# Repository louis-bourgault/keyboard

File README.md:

# keyboard
*my project for hack club blueprint*

## Render (made in blender, not exact but this is what I'm going for. I had some fun with lighting in this one)

### Boring edition without the lighting

My design for a lily58 inspired split wireless keyboard using ergogen and kicad. It uses the NRF52840 chipset, and 3d printed parts mostly

One of my friends has significant wrist pain because his laptop keyboard is terrible. A few months ago we were planning to make a keyboard together and made things in Ergogen but never got that much further than that. Now, I have put things into kicad and done a bit more work in preparing things to be actually manufactured.
This is designed to be pretty much as cheap a keyboard as it is possible to manufacture, aiming for about AU$50 per keyboard (I am making two of these, so more like $100 total). This comes out to about $30 USD per keyboard, $60 total.

## Design
### PCB
- Ergogen for PCB design and layout drafting. It is a very simple, user friendly and powerful program. You define layouts for rows and columns, and nets to connect them
  - Note: In my Ergogen file there is a single net that was not correct, and I had to route manually in KiCad. This is the upper thumb cluster key.
- KiCad for routing the pcb. Ergogen creates the nets, so I only have to route it -- as such, there is no kicad schematic file, just a pcb file that I edited to design
- PCB: AllPcb. They had a cheap offer which let me get everything for a $2, including delivery.

### Case Design:
I use Fusion 360 in school, and am quite used to the program, so that is what I will use. As of November 1 2025, I haven't fully decided on the design -- but what I am thinking is that i will use a clean looking white coloured case, with an oiled plywood or even Jarrah laser cut bottom plate that fits in. My school has a good 3d printer (bambu p1s) and a laser cutter, so I can get everything designed there.
Ergogen outputs a DXF file for the bottom shape of the case, which is defined through the ```outlines``` section of ergogen.yml. This is the shape that I use for the outline of my PCB, so I will need to make an offset line around and use that as the case outline.
Also, since I will be taking this keyboard to and from school, I will make a hinging case to place the two halves in with foam padding for safety.

### Software
I will probably just go with zmk for this. One thing that is important to me is for the keyboard to run both wired and wireless - eg I plug one half with a usb C to A port into a school computer, and then that half talks to the other half and I can use it on computers without Bluetooth support; but I believe that QMK has this function so I will just use that. Potentially, if I have extra time, then I could code something custom in C, but I am not sure whether this is feasible at this point and with exams coming up.

Note: this software is in a seperate repo because of the way that ZMK works. The repo is [louis-bourgault/zmk-config](https://github.com/louis-bourgault/zmk-config)

# Images

# Bill of Materials

|Component Type       |Item Link                                                 |Quantity needed|Relevant Specifications       |Tax % (if not included)|Price each (AUD)|Total Cost (AUD)|Total Cost (USD) (using 1 AUD = 0.65 USD)|Running Cost (AUD|Running Cost (USD)|Note                                                                                                                                                       |
|---------------------|----------------------------------------------------------|---------------|------------------------------|-----------------------|----------------|----------------|-----------------------------------------|-----------------|------------------|-----------------------------------------------------------------------------------------------------------------------------------------------------------|
|Battery * 4          |https://www.aliexpress.com/item/1005006924508264.html?mp=1|1              |3.7v, 400mAh, 53x36x6mm, JSTPH|0.00%                  |$18.40          |$18.40          |$11.96                                   |$18.40           |$11.96            |                                                                                                                                                           |
|NRF52840             |https://www.aliexpress.com/item/1005006035267231.html?    |4              |                              |10.00%                 |$5.65           |$24.86          |$16.16                                   |$43.26           |$28.12            |                                                                                                                                                           |
|Keyboard Switch * 110|https://www.aliexpress.com/item/1005006376024657.html?mp=1|1              |Gateron Brown * 110           |10.00%                 |$18.33          |$20.16          |$13.11                                   |$63.42           |$41.22            |This is using my Welcome Deal on Aliexpress                                                                                                                |
|Keyboard Switch * 10 |https://www.aliexpress.com/item/1005006376024657.html?mp=1|1              |Gateron Yellow * 10           |10.00%                 |$4.70           |$5.17           |$3.36                                    |$68.59           |$44.59            |Supplemental Switches, not on welcome deal so substantially more expensive. Will use different type of switch (linear instead of tactile) for modifier keys|
|Diodes * 200         |https://www.aliexpress.com/item/1005009896621714.html     |1              |Basic 1n4148 diodes           |10.00%                 |$5.94           |$6.53           |$4.25                                    |$75.13           |$48.83            |                                                                                                                                                           |
|PCB * 5              |AllPCB                                                    |1              |                              |0.00%                  |$2.14           |$2.14           |$1.39                                    |$77.27           |$50.22            |already purchased                                                                                                                                          |
|Keycaps * 80         |https://www.aliexpress.com/item/1005007415198959.html?mp=1|2              |                              |10.00%                 |$13.58          |$29.88          |$19.42                                   |$107.14          |$69.64            |                                                                                                                                                           |

# Note on Pricing
Since a lot of these sites have little fees that are hard to deal with on a one by one basis (such as payment processing fees, et cetera). So, the final numbers as given at checkout are slightly different.
Additionally, there is a chance that these prices may fluctuate. If they go up at all, I am able to cover the cost (I am willing to spend a bit of my money on this, and don't need a grant for all of it).

Note: this order actually cost me $2.14, it's just not showing the right amount because that was a one time discount

Prices:
- Aliexpress: AU$114.54
- Allpcb: AU$2.14

Total: AU$116.68
In USD: US$76.20
Note: if I do not qualify for a full support, i can cover a portion of it.

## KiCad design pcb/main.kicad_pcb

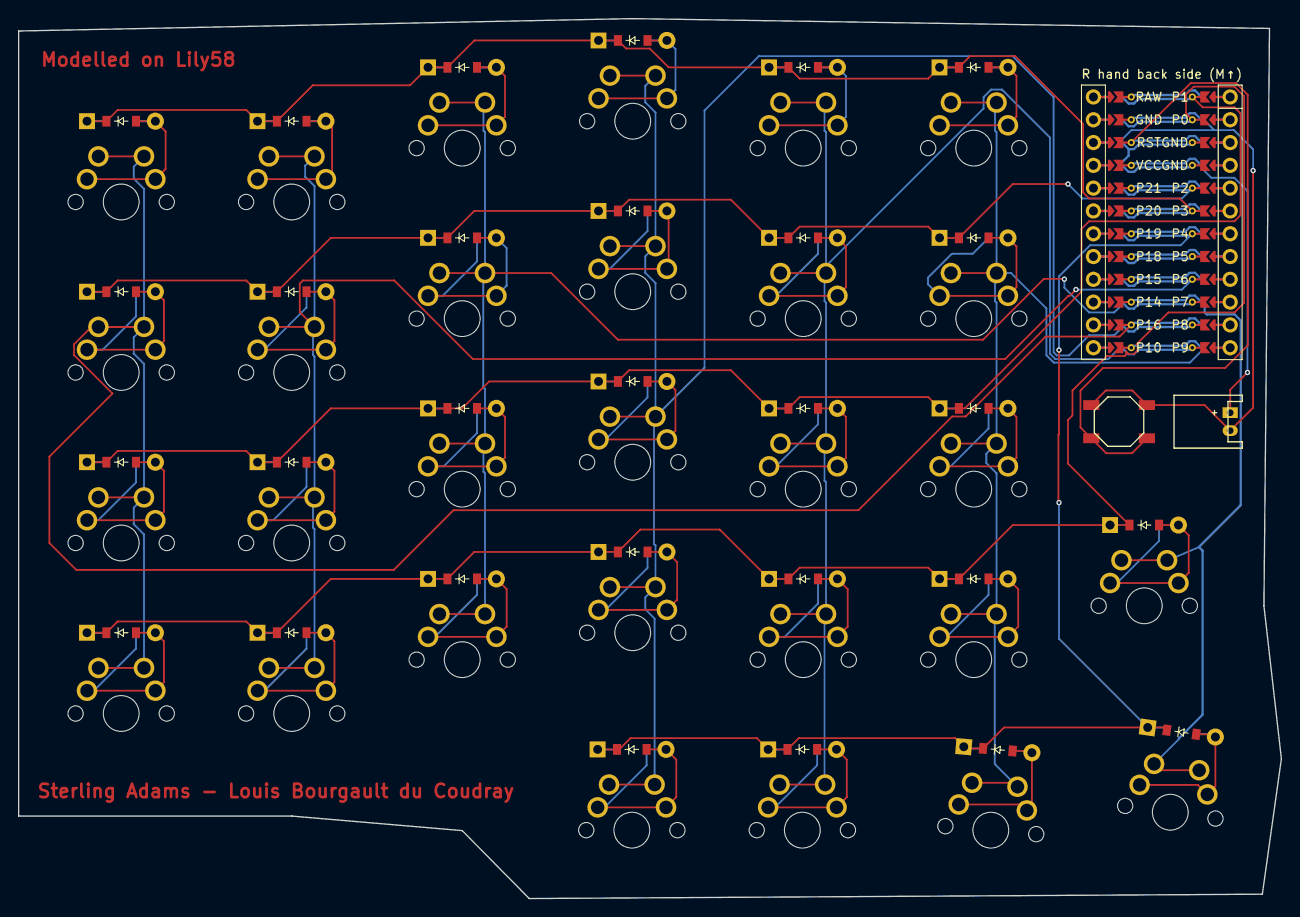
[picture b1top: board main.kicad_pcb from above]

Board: 2 copper layers, 140.7 x 98.1 mm, 61 parts (0 on the bottom side), 44 nets.

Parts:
B1: SW_TACT_ALPS_SKQGABE010
D1, D2, D3, D4, D5, D6, D7, D8, D9, D10, D11, D12, D13, D14, D15, D16, D17, D18, D19, D20, D21, D22, D23, D24, D25, D26, D27, D28, D29: ComboDiode
JST1: JST_PH_S2B-PH-K_02x2.00mm_Angled
MCU1: mcu_supermini_nrf52840
S1, S2, S3, S4, S5, S6, S7, S8, S9, S10, S11, S12, S13, S14, S15, S16, S17, S18, S19, S20, S21, S22, S23, S24, S25, S26, S27, S28, S29: MX

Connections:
1_top: D26.2, S26.2
2_top: D27.2, S27.2
3_top: D28.2, S28.2
4_top: D29.2, S29.2
GND: B1.1, JST1.2, MCU1.103, MCU1.104, MCU1.123
P0: D1.1, D5.1, D9.1, D13.1, D17.1, D21.1, D25.1, MCU1.102
P1: D2.1, D6.1, D10.1, D14.1, D18.1, D22.1, MCU1.101
P2: D3.1, D7.1, D11.1, D15.1, D19.1, D23.1, MCU1.105
P3: D4.1, D8.1, D12.1, D16.1, D20.1, D24.1, MCU1.106
P4: D26.1, D27.1, D28.1, D29.1, MCU1.107
P6: MCU1.109, S5.1, S6.1, S7.1, S8.1
P7: MCU1.110, S9.1, S10.1, S11.1, S12.1
P8: MCU1.111, S13.1, S14.1, S15.1, S16.1, S26.1
P9: MCU1.112, S17.1, S18.1, S19.1, S20.1, S27.1
P10: MCU1.113, S21.1, S22.1, S23.1, S24.1, S28.1
P14: MCU1.115, S29.1
P16: MCU1.114, S1.1, S2.1, S3.1, S4.1
RST: B1.2, MCU1.122
VCC: JST1.1, MCU1.121
index_home: D18.2, S18.2
index_lower: D17.2, S17.2
index_num: D20.2, S20.2
index_upper: D19.2, S19.2
inner_home: D22.2, S22.2
inner_lower: D21.2, S21.2
inner_num: D24.2, S24.2
inner_upper: D23.2, S23.2
innest_lower: D25.2, S25.2
middle_home: D14.2, S14.2
middle_lower: D13.2, S13.2
middle_num: D16.2, S16.2
middle_upper: D15.2, S15.2
outer_home: D2.2, S2.2
outer_lower: D1.2, S1.2
outer_num: D4.2, S4.2
outer_upper: D3.2, S3.2
pinkie_home: D6.2, S6.2
pinkie_lower: D5.2, S5.2
pinkie_num: D8.2, S8.2
pinkie_upper: D7.2, S7.2
ring_home: D10.2, S10.2
ring_lower: D9.2, S9.2
ring_num: D12.2, S12.2
ring_upper: D11.2, S11.2

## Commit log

2025-11-01 added ergogen config
2025-11-01 exported gerbers ready to put on allpcb
2025-11-01 added images and improved readme
2025-11-01 updated readme and added gerbers.
2025-11-01 Initial bill of materials draft
2025-11-01 Update README.md
    fixed zmk
2025-11-02 added fusion 360 document and stl files for prints
2025-11-02 update ergogen config
2025-11-02 added link to zmk
2025-11-05 added screenshot of case design
2025-11-06 Updated Bill of Materials to final version
2025-11-06 trimmed tracking urls from links
2025-11-06 added gcode from Bambu Studio for printing
2025-11-06 removed more tracking links
2025-11-08 Updated pricing with new things that had sold out, and cart screenshots
2025-11-08 added bnoted allpcb order
2025-11-08 exported newest versions of step and f3d files ready for submitting
2025-11-15 Updated BOM
2025-11-16 Added new render
2025-12-03 things
2026-01-18 pcb annotations
2026-01-28 Added new case that takes into account cutouts for the plate
